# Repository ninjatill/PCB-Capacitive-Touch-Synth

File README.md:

# PCB-Capacitive-Touch-Synth
A Raspberry Pi-based synthesizer with capacitive touch keys directly on a PCB.

## Licensing

### Hardware
All files in `/hardware` are licensed under:

CC BY-NC-SA 4.0

### Firmware
All files in `/firmware` are licensed under:

GPLv3

## Concept
The PCB-Capacitive-Touch-Synth started as a sub-component of a larger science fair project. For my daughter's next science fair project (5th grade), she chose to create Plasma Speakers as we saw on the Franzoli Electronics YouTube page. The plasma speakers are flyback transformers that create a high-voltage arc (which ionizes the air into plasma). The frequeny of the arc creates audio tones. On Franzoli's demonstration videos, he plays MIDI-style music with each speaker acting as a left or right channel/voice. That is the concept we want to re-create.

If we re-create the plasma speakers, then how do we make then into an interactive display for the fair? Well, what if we had 2 midi-controller keyboards hooked up to a host PC. The host PC would do the heavy lifting of audio generation and output to the plasma speakers. Each keyboard would play its notes through either the left or right channel respectively. That's the main idea: 2 keyboards, a host PC, and plasma speakers.

To source the midi keyboards, you could go to Amazon and pick up a 30$-70$ keyboard (higher-end small midi keyboards can run upwards of 200-500$). But, commercial MIDI controllers usually do not output sound directly, it requires a host PC; so its usefullness outside the fair display is limited. The size and scale of the keyboards should be small (to match the entire setup which is portable and compact for a 36"-48" display.) The speakers on Franzoli's demos are very industrial/scientific looking. I thought commercial keyboards would look out of place or be too expensive. So I had a concept of creating keyboards printed on PCBs using capacitive touch buttons. The keyboards would be build to our specific needs and we can build in many features because of the DIY nature.

I decided the best course of action was to have my daughter re-create Fanzoli's Easy-Flyback circuits. It will teach her basic electrical components, schematic creation and PCB layout and fabrication. I think that's a wealth of knowledge for a 10 year old (maybe 11 by the time this comes to fruition). I will handle creating the PCB Capacitive Touch Synthesizer. It is a large complex project and is difficult for my own skill set.

## Documentation

- [Design Notes](docs/design-notes.md)

## Concept to Schematic
As an electrical engineer, I have created PCBs for simple devices. A capacitive touch synthesizer is the largest project/PCB I will have created. So, to jumpstart the project, I consulted my new "friend", ChatGPT. ChatGPT was able to answer questions and make recommendations faster than I could search DigiKey/Mouser, review datasheets, and find the right combination of ICs. But to be clear, I was driving the design. I wanted specific features and ChatGPT helped me realize those features faster than I could alone.

I started with the following design critera
- The front of the keyboard should be as flat as possible both for aestectic and functional reasons.
  - Aesthetically, I don't want a lot of clutter on the front of the board.
  - Functionally, Children will be interacting with this. I don't want exposed chip leads or solder pads. I also don't want through hole components sticking up with sharp edges. If kids can touch it, they will.
- The keyboard should be as small as possible but still allowing for decent usability (key widths wide enough for easy touch, etc.)
  
From the design criteria, we landed with some of the following choices:
- We will use capacitive touch sensors for the piano keys. Capacitive touch reduces mechanical parts that need fabricated (via 3D printing). It's more touch-friendly than many momentary push buttons.
- We will keep all IC's on the back of the board. Only LEDs and a volume knob will protrude from the front.
- We will use only surface mount components (to eliminate protrusions through the board and maintain the flat asthetic.)
- We will 3D print a back cover that serves 2 purposes: 
  - It will cover the back circuitry to prevent tampering.
  - It will raise the PCB off the display surface by a comfortable distance (and tilt it forward a few degrees) to increase usability.

## Basic Functionality
- The synthesizer will funtion in two main modes: standalone and MIDI.
  - In standalone mode, the keyboard will generate its own sounds via speaker or headphones.
  - In MIDI mode, the keyboard will send MIDI commands to a host PC (this is the intended mode for the science fair.

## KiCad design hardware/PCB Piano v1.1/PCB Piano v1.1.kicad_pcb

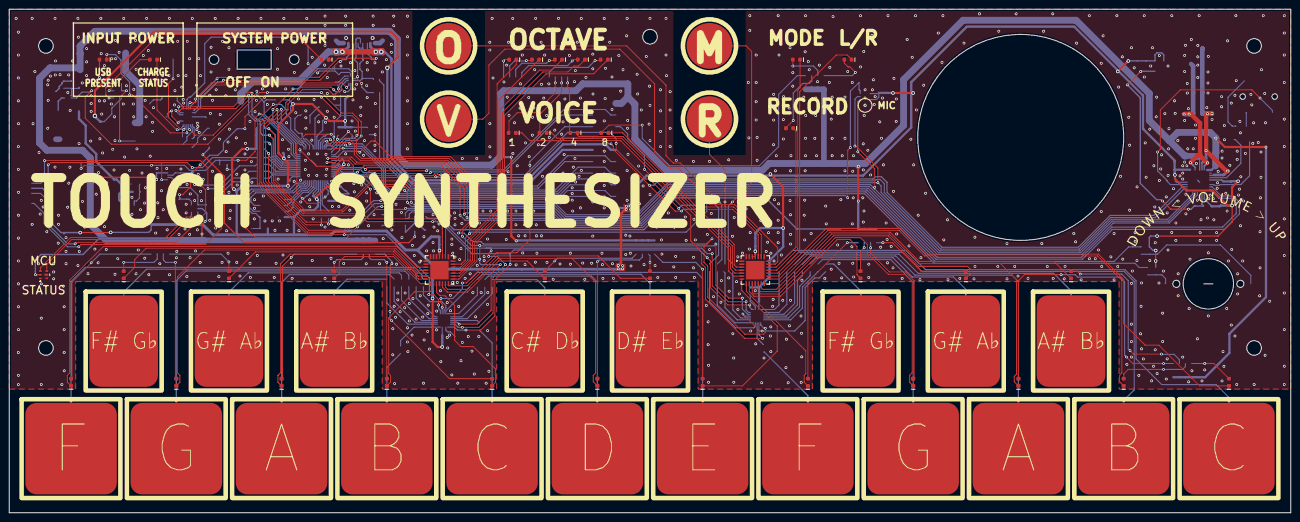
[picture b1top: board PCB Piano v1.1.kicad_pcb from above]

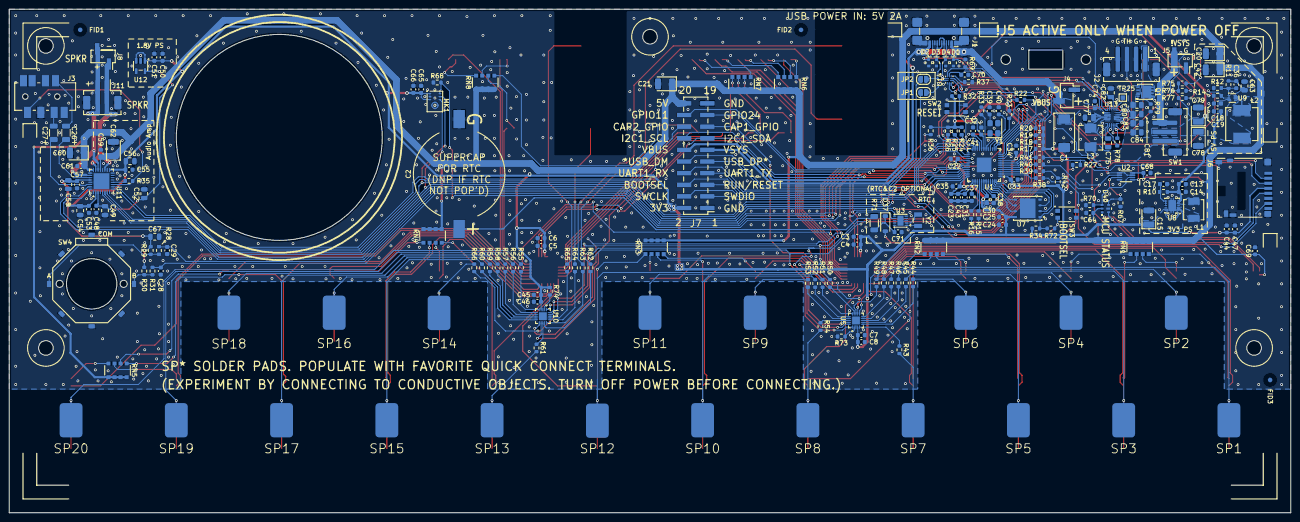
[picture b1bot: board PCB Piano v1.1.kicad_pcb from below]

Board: 2 copper layers, 280.0 x 110.0 mm, 284 parts (216 on the bottom side), 222 nets.

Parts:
C1: 47uF; CP_EIA-7343-43_Kemet-X
C2: 1F; SuperCap_HType_FoldedOutLegs
C3, C6, C8, C13, C18, C23, C24, C31, C37, C44, C45, C50, C66, C74: 1uF; C_0603_1608Metric
C4, C5, C7, C14, C17, C19, C22, C25, C28, C29, C30, C32, C33, C34, C35, C38, C41, C43, C46, C47, C48, C51, C53, C55, C57, C59, C61, C64, C65, C68, C69, C70, C71: .1uF; C_0603_1608Metric
C15, C20, C21, C42, C60, C62, C78, C79: 47uF; CP_EIA-3528-15_AVX-H
C26, C27: 100uF; C_1206_3216Metric
C36: 220pF; C_0603_1608Metric
C39, C40: 27pF; C_0603_1608Metric
C49, C52, C54, C56, C58, C63, C67, C77, C80, C81, C82, C83, C84: 10uF; C_0805_2012Metric
C75: 22nF; C_0805_2012Metric
D1, D2, D3, D4: ESD321; D_SOD-523
D5, D6, D7, D8, D9, D10, D11, D12, D13, D14, D15, D16, D17, D18, D19, D20, D21, D22, D23, D24, D25, D26, D27, D28, D29, D30, D31, D32, D33, D34, D35, D36, D43, D44, D45: 3.3fV 180mcd; LED_0603_1608Metric
D37: Schottky; D_SOD-123
D40, D41: Dotstar LED; APA102-2020
FID1, FID2, FID3: Fiducial; Fiducial_1mm_Mask3mm
H1, H2, H3, H4, H5: MountingHole; MountingHole_3.2mm_M3
J1: USB4110-GF-A; USB_C_Receptacle_GCT_USB4110
J2: JST PH 4-PIN; JST_PH_B4B-PH-SM4-TB_1x04-1MP_P2.00mm_Vertical
J3: 3.5mm TRRS; AudioJack_TRS_Switch_TR1R2S_SJ3-35024K-SMT-TR
J4, J5, J8: PinHeader 1x02 SMT; PinHeader_1x02_P2.54mm_Vertical_SMD_Pin1Right
J6: micro SD Card Slot; microSD_HC_Hirose_DM3D-SF
J7: PinHeader 2x10 SMT Odd_Even; PinHeader_2x10_P2.54mm_Vertical_SMD
J11: JST-PH 2-PIN SMT; JST_PH_B2B-PH-SM4-TB_1x02-1MP_P2.00mm_Vertical
JP1, JP2: SolderJumper_2_Open; SolderJumper-2_P1.3mm_Open_RoundedPad1.0x1.5mm
L1: 2.2uH; L_Bourns_SRP4020T_4.06x4.45x2.0mm
L2: 2.2uH; L_Pulse_BMRB00060630_7.3x6.6mm
L3: 1uH; L_Sumida_0530CDMCCDS-1R0MC_5.4x5.2mm
MK1: MEMS I2S Microphone; InvenSense_ICS-43432-7_4x3mm
Q1: P-Ch Power MOSFET; PPAK_3x3
R10: 100; R_0603_1608Metric
R11: 732k; R_0603_1608Metric
R12, R14, R25, R26, R27, R36, R37, R67, R69, R70, R73, R74, R79: 100k; R_0603_1608Metric
R15, R16, R38, R39, R40, R41: 27; R_0603_1608Metric
R17, R18, R19, R20: 4.7k; R_0603_1608Metric
R22, R23, R24, R28, R29, R30, R31, R32, R34, R42, R43, R44, R45, R46, R47, R48, R49, R50, R51, R52, R53, R54, R55, R56, R57, R58, R59, R60, R61, R62, R63, R64, R65, R66, R68, R78: 10k; R_0603_1608Metric
R33, R72: 1k; R_0603_1608Metric
R35: 2.2k; R_0603_1608Metric
R71: 150; R_1206_3216Metric
R75, R76, R77: 1.5k; R_0603_1608Metric
RN1, RN2, RN3, RN4, RN5, RN6, RN7, RN8: 180 Ohm; R_Array_Convex_4x1206
SP1, SP2, SP3, SP4, SP5, SP6, SP7, SP8, SP9, SP10, SP11, SP12, SP13, SP14, SP15, SP16, SP17, SP18, SP19, SP20: Pad_Solder_SMT_5x7mm
SW1: JST-PH 1x03 SMT; JST_PH_B3B-PH-SM4-TB_1x03-1MP_P2.00mm_Vertical
SW2, SW3: Pushbutton MO; SW_SWT0115-020025SSA_REVA
SW4: MER1045-24; Switch_RotaryEncoder_MER1045-24
SWCUT1: MFS 126 D; Switch_Slide_MFS126E_PanelCutout
TP1, TP3, TP5, TP7, TP8, TP10, TP12, TP13, TP15, TP17, TP19, TP20: Touchpad_WhiteKey
TP2, TP4, TP6, TP9, TP11, TP14, TP16, TP18: Touchpad_BlackKey
TP21, TP22, TP23, TP24: Touchpad_Circle_10mm
TP25: TestPoint_Square; TestPoint_Pad_1.0x1.0mm
U1: RP2040; QFN-56-1EP_7x7mm_P0.4mm_EP3.2x3.2mm
U2: Dual Line Buffer; VSSOP-8_2.3x2mm_P0.5mm
U3: RTC; DFN-10-1EP_2.6x2.6mm_P0.5mm_EP1.3x2.2mm
U4, U6: LED Controller; NXP_HVQFN-28_6mmx6mmx0.85mm
U5, U10: Touch Controller; VQFN-20-1EP_3x3mm_P0.4mm_EP1.7x1.7mm
U7: 128MBit; WSON-8-1EP_6x5mm_P1.27mm_EP3.4x4.3mm
U8: 3.3V; Texas_DRC0010J
U9: 5V; SOT-563
U11: Audio DAC Class-D I2S/I2C; Texas_RHB0032E_VQFN-32-1EP_5x5mm_P0.5mm_EP3.45x3.45mm
U12: 1.8V; SOT-23-5
U13: USB C Sink Ctrl/Batt Chgr; QFN-22_2.5x3.2mm_P0.4mm
U14: 1:2 USB MUX; TQFN-10_ZL_1.6x1.3mm_P0.4mm
Y1: 12MHz; Crystal_SMD_Abracon_ABM8G-4Pin_3.2x2.5mm
Y2: 32.768kHz; Crystal_Kyocera_DT32_3.2x1.5mm

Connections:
+1V1: C37.1, C38.1, C41.1, U1.23 (DVDD), U1.45 (VREG_VOUT), U1.50 (DVDD)
+1V8: C48.1, C49.1, C52.1, U11.3 (DVDD), U12.5 (OUT)
+3.3V: C3.1, C4.1, C5.1, C6.1, C7.1, C8.1, C15.1, C22.1, C23.1, C24.1, C25.1, C30.1, C31.1, C32.1, C33.1, C34.1, C35.1, C43.1, C44.1, C45.1, C46.1, C47.1, C50.1, C51.1, C53.1, C54.1, C55.1, C56.1, C57.1, C58.1, C65.1, C66.1, C67.1, J6.4 (VDD), J7.2, MK1.1 (LR), MK1.3 (VDD), R17.1, R18.1, R19.1, R20.1, R22.1, R23.1, R24.1, R25.1, R26.1, R27.1, R29.2, R30.2, R32.1, R34.1, R36.1, R42.1, R74.1, U1.1 (IOVDD), U1.10 (IOVDD), U1.22 (IOVDD), U1.33 (IOVDD), U1.42 (IOVDD), U1.43 (ADC_AVDD), U1.44 (VREG_VIN), U1.48 (USB_VDD), U1.49 (IOVDD), U4.25 (VDD), U5.4 (VDD), U6.25 (VDD), U6.26 (A0), U7.8 (VCC), U8.1 (VOUT), U8.10 (FB), U10.4 (VDD), U11.2 (IOVDD), U11.17 (AVDD), U11.28 (HPVDD), U12.1 (IN), U12.3 (EN)
+5V: C20.1, C21.1, C36.1, C42.1, C59.1, C60.1, C61.1, C62.1, C63.1, C64.1, C68.1, C69.1, D40.2 (VDD), D41.2 (VDD), J7.20, R11.1, RN1.5 (R4.2), RN1.6 (R3.2), RN1.7 (R2.2), RN1.8 (R1.2), RN2.5 (R4.2), RN2.6 (R3.2), RN2.7 (R2.2), RN2.8 (R1.2), RN3.5 (R4.2), RN3.6 (R3.2), RN3.7 (R2.2), RN3.8 (R1.2), RN4.5 (R4.2), RN4.6 (R3.2), RN4.7 (R2.2), RN4.8 (R1.2), RN5.5 (R4.2), RN5.6 (R3.2), RN5.7 (R2.2), RN5.8 (R1.2), RN6.5 (R4.2), RN6.6 (R3.2), RN6.7 (R2.2), RN6.8 (R1.2), RN7.5 (R4.2), RN7.6 (R3.2), RN7.7 (R2.2), RN7.8 (R1.2), RN8.5 (R4.2), RN8.6 (R3.2), RN8.7 (R2.2), RN8.8 (R1.2), U2.8 (VCC), U9.6 (VOUT), U11.21 (SPKVDD), U11.24 (SPKVDD)
/LED/I2C1_SCL: J7.14, R20.2, U1.9 (GPIO7), U3.7 (SCL), U4.23 (SCL), U6.23 (SCL), U11.10 (SCL), U13.16 (SCL)
/LED/I2C1_SDA: J7.13, R19.2, U1.8 (GPIO6), U3.6 (SDA), U4.24 (SDA), U6.24 (SDA), U11.9 (SDA), U13.15 (SDA)
/LED/LED_100: D5.1 (K), U4.3 (LED0)
/LED/LED_101: D6.1 (K), U4.4 (LED1)
/LED/LED_102: D7.1 (K), U4.5 (LED2)
/LED/LED_103: D8.1 (K), U4.6 (LED3)
/LED/LED_104: D9.1 (K), U4.7 (LED4)
/LED/LED_105: D10.1 (K), U4.8 (LED5)
/LED/LED_106: D11.1 (K), U4.9 (LED6)
/LED/LED_107: D12.1 (K), U4.10 (LED7)
/LED/LED_108: D13.1 (K), U4.12 (LED8)
/LED/LED_109: D14.1 (K), U4.13 (LED9)
/LED/LED_110: D15.1 (K), U4.14 (LED10)
/LED/LED_111: D29.1 (K), U4.15 (LED11)
/LED/LED_112: D28.1 (K), U4.16 (LED12)
/LED/LED_113: D27.1 (K), U4.17 (LED13)
/LED/LED_114: D26.1 (K), U4.18 (LED14)
/LED/LED_115: D25.1 (K), U4.19 (LED15)
/LED/LED_200: D30.1 (K), U6.3 (LED0)
/LED/LED_201: D31.1 (K), U6.4 (LED1)
/LED/LED_202: D32.1 (K), U6.5 (LED2)
/LED/LED_203: D33.1 (K), U6.6 (LED3)
/LED/LED_204: D16.1 (K), U6.7 (LED4)
/LED/LED_205: D17.1 (K), U6.8 (LED5)
/LED/LED_206: D18.1 (K), U6.9 (LED6)
/LED/LED_207: D19.1 (K), U6.10 (LED7)
/LED/LED_208: D20.1 (K), U6.12 (LED8)
/LED/LED_209: D21.1 (K), U6.13 (LED9)
/LED/LED_210: D22.1 (K), U6.14 (LED10)
/LED/LED_211: D23.1 (K), U6.15 (LED11)
/LED/LED_212: D24.1 (K), U6.16 (LED12)
/LED/LED_213: D36.1 (K), U6.17 (LED13)
/LED/LED_214: D35.1 (K), U6.18 (LED14)
/LED/LED_215: D34.1 (K), U6.19 (LED15)
/LED/LED_~EN: R36.2, U1.31 (GPIO20), U4.20 (~OE), U6.20 (~OE)
/MCU/5V_EN: R14.2, U1.30 (GPIO19), U9.2 (EN)
/MCU/AMP_INT: U1.41 (GPIO29/ADC3), U11.32 (GPIO1)
/MCU/AMP_~RST: U1.37 (GPIO25), U11.31 (~RESET)
/MCU/BOOTSEL: J7.6, R72.2, SW3.3
/MCU/CAP1_~INT: R23.2, U1.18 (GPIO15), U5.11 (*INT)
/MCU/CAP2_~INT: R24.2, U1.27 (GPIO16), U10.11 (*INT)
/MCU/CAPx_~RST: R25.2, U1.28 (GPIO17), U5.19 (*RESET), U10.19 (*RESET)
/MCU/CHG_~INT: R22.2, U1.12 (GPIO9), U13.8 (~INT)
/MCU/DS_~EN: R26.2, U1.29 (GPIO18), U2.1, U2.7
/MCU/ENC_A: C29.1, R28.2, U1.32 (GPIO21)
/MCU/ENC_B: C28.1, R31.1, U1.34 (GPIO22)
/MCU/GPIO11: J7.18, U1.14 (GPIO11)
/MCU/GPIO24: J7.17, U1.36 (GPIO24)
/MCU/I2C0_SCL: R18.2, U1.7 (GPIO5), U5.1 (SCL), U10.1 (SCL)
/MCU/I2C0_SDA: R17.2, U1.6 (GPIO4), U5.20 (SDA), U10.20 (SDA)
/MCU/I2S_BCLK: MK1.6 (SCK), U1.38 (GPIO26/ADC0), U11.7 (BCLK)
/MCU/I2S_LRCLK: MK1.5 (WS), U1.39 (GPIO27/ADC1), U11.6 (WCLK)
/MCU/I2S_SDATA: U1.40 (GPIO28/ADC2), U11.5 (DIN)
/MCU/I2S_SDATA_MIC: MK1.7 (SD), R68.2, U1.35 (GPIO23)
/MCU/MCU_DM: R15.2, U14.6 (D-)
/MCU/MCU_DP: R16.2, U14.7 (D+)
/MCU/RTC_BATT: C2.1, R71.1
/MCU/RTC_VDD: C71.1, D37.1 (K), R71.2, U3.10 (VDD)
/MCU/RUN: J7.5, R32.2, SW2.3, U1.26 (RUN)
/MCU/SD_DET: J6.10 (DET_A), R27.2, U1.11 (GPIO8)
/MCU/SPI0_MISO: J6.7 (DAT0), R38.1
/MCU/SPI0_MOSI: J6.3 (CMD), R41.1, U2.5
/MCU/SPI0_SCK: J6.5 (CLK), R40.1, U2.2
/MCU/SPI0_~CS: J6.2 (DAT3/CD), R39.1, R42.2
/MCU/SWCLK: J7.4, U1.24 (SWCLK)
/MCU/SWDIO: J7.3, U1.25 (SWDIO)
/MCU/UART1_RX: J7.8, U1.16 (GPIO13)
/MCU/UART1_TX: J7.7, U1.15 (GPIO12)
/MCU/USB_SEL: R69.1, U1.13 (GPIO10), U14.10 (SEL)
/audio/HP_L: C26.1, U11.27 (HPL)
/audio/HP_R: C27.1, U11.30 (HPR)
/audio/SPKM: J8.1, J11.1, U11.19 (SPKM), U11.23 (SPKM)
/audio/SPKP: J8.2, J11.2, U11.22 (SPKP), U11.26 (SPKP)
/debug/CAP1_GPIO: J7.15, U5.12 (GPIO12)
/debug/CAP2_GPIO: J7.16, U10.12 (GPIO12)
/debug/DEBUG_DM: J7.10, JP2.1 (A)
/debug/DEBUG_DP: J7.9, JP1.1 (A)
/power/USB_CC1: D1.1 (K), J1.A5 (CC1), U13.1 (CC1)
/power/USB_CC2: D2.1 (K), J1.B5 (CC2), U13.22 (CC2)
/power/USB_DM: D3.1 (K), J1.A6 (D+), J1.B6 (D+), JP2.2 (B), U14.2 (Y-)
/power/USB_DP: D4.1 (K), J1.A7 (D-), J1.B7 (D-), JP1.2 (B), U14.1 (Y+)
/power/battery charger 2/BATT_POS: J2.1, Q1.D
/power/battery charger 2/CHG_BATT: C80.1, C81.1, Q1.S, U13.12 (BATTSNS), U13.14 (BATT)
/power/battery charger 2/CHG_DM: U13.20 (D-), U14.4 (M-)
/power/battery charger 2/CHG_DP: U13.21 (D+), U14.5 (M+)
/power/battery charger 2/CHG_OUT: C83.1, C84.1, D37.2 (A), L3.1, R75.1, R76.1, SW1.3 (C), U13.13 (SYS)
/power/battery charger 2/CHG_VCC: C70.1, C82.1, U13.19 (VCC), U14.9 (VDD)
/power/battery charger 2/TH1_POS: J2.3, R78.2, U13.10 (NTC1)
/touch/TOUCH_100: R43.2, SP7.1 (1_1), TP7.1
/touch/TOUCH_101: R44.2, SP6.1 (1_1), TP6.1
/touch/TOUCH_102: R45.2, SP5.1 (1_1), TP5.1
/touch/TOUCH_103: R46.2, SP4.1 (1_1), TP4.1
/touch/TOUCH_104: R47.2, SP3.1 (1_1), TP3.1
/touch/TOUCH_105: R48.2, SP2.1 (1_1), TP2.1
/touch/TOUCH_106: R49.2, SP1.1 (1_1), TP1.1
/touch/TOUCH_107: R50.2, SP12.1 (1_1), TP12.1
/touch/TOUCH_108: R51.2, SP11.1 (1_1), TP11.1
/touch/TOUCH_109: R52.2, SP10.1 (1_1), TP10.1
/touch/TOUCH_110: R53.2, SP9.1 (1_1), TP9.1
/touch/TOUCH_111: R54.2, SP8.1 (1_1), TP8.1
/touch/TOUCH_200: R55.2, SP20.1 (1_1), TP20.1
/touch/TOUCH_201: R56.2, SP19.1 (1_1), TP19.1
/touch/TOUCH_202: R57.2, SP18.1 (1_1), TP18.1
/touch/TOUCH_203: R58.2, SP17.1 (1_1), TP17.1
/touch/TOUCH_204: R59.2, SP16.1 (1_1), TP16.1
/touch/TOUCH_205: R60.2, SP15.1 (1_1), TP15.1
/touch/TOUCH_206: R61.2, SP13.1 (1_1), TP13.1
/touch/TOUCH_207: R62.2, TP22.1
/touch/TOUCH_208: R63.2, TP21.1
/touch/TOUCH_209: R64.2, TP24.1
/touch/TOUCH_210: R65.2, TP23.1
/touch/TOUCH_211: R66.2, SP14.1 (1_1), TP14.1
GND: C1.2, C2.2, C3.2, C4.2, C5.2, C6.2, C7.2, C8.2, C13.2, C14.2, C15.2, C17.2, C18.2, C19.2, C20.2, C21.2, C22.2, C23.2, C24.2, C25.2, C28.2, C29.2, C30.2, C31.2, C32.2, C33.2, C34.2, C35.2, C37.2, C38.2, C39.2, C40.2, C41.2, C42.2, C43.2, C44.2, C45.2, C46.2, C47.2, C48.2, C49.2, C50.2, C51.2, C52.2, C53.2, C54.2, C55.2, C56.2, C57.2, C58.2, C59.2, C60.2, C61.2, C62.2, C63.2, C64.2, C65.2, C66.2, C67.2, C68.2, C69.2, C70.2, C71.2, C74.2, C77.2, C78.2, C79.2, C80.2, C81.2, C82.2, C83.2, C84.2, D1.2 (A), D2.2 (A), D3.2 (A), D4.2 (A), D40.5 (GND), D41.5 (GND), D45.1 (K), J1.A1 (GND), J1.A12 (GND), J1.B1 (GND), J1.B12 (GND), J1.SH (SHIELD), J2.2, J2.4, J2.MP (MountPin), J3.2 (R2), J4.1, J5.1, J6.6 (VSS), J6.9 (DET_B), J6.SH (SHIELD), J7.1, J7.19, J11.MP (MountPin), MK1.2 (CONFIG), MK1.4 (GND), R12.1, R14.1, R37.1, R67.2, R68.1, R69.2, R70.2, R73.2, R79.2, SW1.MP, SW2.1, SW2.2, SW3.1, SW3.2, SW4.C, SW4.GND (MountPoints), U1.19 (TESTEN), U1.57 (GND), U2.4 (GND), U3.3 (CLKOE), U3.5 (VSS), U3.11 (EP), U4.1 (A3), U4.2 (A4), U4.11 (VSS), U4.21 (A5), U4.22 (EXTCLK), U4.26 (A0), U4.27 (A1), U4.28 (A2), U4.29 (VSS), U5.3 (GND), U5.21 (EP), U6.1 (A3), U6.2 (A4), U6.11 (VSS), U6.21 (A5), U6.22 (EXTCLK), U6.27 (A1), U6.28 (A2), U6.29 (VSS), U7.4 (GND), U7.9 (EP), U8.3 (PGND), U8.9 (GND), U8.11 (PGND), U9.4 (GND), U10.3 (GND), U10.21 (EP), U11.1 (IOVSS), U11.16 (AVSS), U11.18 (DVSS), U11.20 (SPKVSS), U11.25 (SPKVSS), U11.29 (HPVSS), U11.33 (EP), U12.2 (GND), U13.5 (PGND), U13.18 (AGND), U14.3 (GND), Y1.2 (G), Y1.4 (G)
unnamed: C39.1, R33.1, Y1.3
unnamed: D5.2 (A), RN1.4 (R4.1)
unnamed: D6.2 (A), RN1.3 (R3.1)
unnamed: D7.2 (A), RN1.2 (R2.1)
unnamed: D8.2 (A), RN1.1 (R1.1)
unnamed: D9.2 (A), RN2.4 (R4.1)
unnamed: D10.2 (A), RN2.3 (R3.1)
unnamed: D11.2 (A), RN2.2 (R2.1)
unnamed: D12.2 (A), RN2.1 (R1.1)
unnamed: D13.2 (A), RN3.4 (R4.1)
unnamed: D14.2 (A), RN3.3 (R3.1)
unnamed: D15.2 (A), RN3.2 (R2.1)
unnamed: D16.2 (A), RN3.1 (R1.1)
unnamed: D17.2 (A), RN4.4 (R4.1)
unnamed: D18.2 (A), RN4.3 (R3.1)
unnamed: D19.2 (A), RN4.2 (R2.1)
unnamed: D20.2 (A), RN4.1 (R1.1)
unnamed: D21.2 (A), RN5.1 (R1.1)
unnamed: D22.2 (A), RN5.2 (R2.1)
unnamed: D23.2 (A), RN5.3 (R3.1)
unnamed: D24.2 (A), RN5.4 (R4.1)
unnamed: D25.2 (A), RN6.1 (R1.1)
unnamed: D26.2 (A), RN6.2 (R2.1)
unnamed: D27.2 (A), RN6.3 (R3.1)
unnamed: D28.2 (A), RN6.4 (R4.1)
unnamed: D29.2 (A), RN7.1 (R1.1)
unnamed: D30.2 (A), RN8.1 (R1.1)
unnamed: D31.2 (A), RN7.4 (R4.1)
unnamed: D32.2 (A), RN7.3 (R3.1)
unnamed: D33.2 (A), RN7.2 (R2.1)
unnamed: D34.2 (A), RN8.2 (R2.1)
unnamed: D35.2 (A), RN8.3 (R3.1)
unnamed: D36.2 (A), RN8.4 (R4.1)
unnamed: D40.3 (CKI), R70.1, U2.6
unnamed: D40.1 (CKO), D41.3 (CKI)
unnamed: D40.6 (SDI), R67.1, U2.3
unnamed: D40.4 (SDO), D41.6 (SDI)
unnamed: D43.2 (A), R75.2
unnamed: D43.1 (K), U13.9 (PG/NTC2)
unnamed: D44.2 (A), R76.2
unnamed: D44.1 (K), U13.11 (STAT/IB)
unnamed: D45.2 (A), R77.2
unnamed: C27.2, J3.3 (R1)
unnamed: J3.1 (S), R35.2, U11.11 (VOL/MICDET)
unnamed: C26.2, J3.8 (T)
unnamed: J5.2, SW1.1 (A)
unnamed: Q1.G, R79.1
unnamed: R28.1, R29.1, SW4.A
unnamed: R30.1, R31.2, SW4.B
unnamed: R38.2, U1.2 (GPIO0)
unnamed: R39.2, U1.3 (GPIO1)
unnamed: R40.2, U1.4 (GPIO2)
unnamed: R41.2, U1.5 (GPIO3)
unnamed: U1.52 (QSPI_SCLK), U7.6 (CLK)
unnamed: U1.53 (QSPI_SD0), U7.5 (DI/IO_{0})
unnamed: U1.55 (QSPI_SD1), U7.2 (DO/IO_{1})
unnamed: U1.54 (QSPI_SD2), U7.3 (~WP/IO_{2})
unnamed: U1.51 (QSPI_SD3), U7.7 (~HOLD/~RESET/IO_{3})
unnamed: R16.1, U1.46 (USB_DM)
unnamed: R15.1, U1.47 (USB_DP)
unnamed: C40.1, U1.20 (XIN), Y1.1
unnamed: R33.2, U1.21 (XOUT)
unnamed: R34.2, R72.1, U1.56 (~QSPI_SS), U7.1 (~CS)
unnamed: U3.1 (OSCI), Y2.2
unnamed: U3.2 (OSCO), Y2.1
unnamed: R73.1, U5.2 (ADD_SEL)
unnamed: R43.1, U5.5 (BUTTON0)
unnamed: R44.1, U5.6 (BUTTON1)
unnamed: R45.1, U5.7 (BUTTON2)
unnamed: R46.1, U5.8 (BUTTON3)
unnamed: R47.1, U5.9 (BUTTON4)
unnamed: R48.1, U5.10 (BUTTON5)
unnamed: R49.1, U5.13 (BUTTON6)
unnamed: R50.1, U5.14 (BUTTON7)
unnamed: R51.1, U5.15 (BUTTON8)
unnamed: R52.1, U5.16 (BUTTON9)
unnamed: R53.1, U5.17 (BUTTON10)
unnamed: R54.1, U5.18 (BUTTON11)
unnamed: C17.1, R10.2, U8.6 (EN), U8.7 (PS/SYNC), U8.8 (VINA)
unnamed: L1.1, U8.4 (L1)
unnamed: L1.2, U8.2 (L2)
unnamed: C36.2, R11.2, R12.2, U9.1 (FB)
unnamed: L2.1, U9.5 (SW)
unnamed: R74.2, U10.2 (ADD_SEL)
unnamed: R55.1, U10.5 (BUTTON0)
unnamed: R56.1, U10.6 (BUTTON1)
unnamed: R57.1, U10.7 (BUTTON2)
unnamed: R58.1, U10.8 (BUTTON3)
unnamed: R59.1, U10.9 (BUTTON4)
unnamed: R60.1, U10.10 (BUTTON5)
unnamed: R61.1, U10.13 (BUTTON6)
unnamed: R62.1, U10.14 (BUTTON7)
unnamed: R63.1, U10.15 (BUTTON8)
unnamed: R64.1, U10.16 (BUTTON9)
unnamed: R65.1, U10.17 (BUTTON10)
unnamed: R66.1, U10.18 (BUTTON11)
unnamed: R35.1, U11.12 (MICBIAS)
unnamed: R78.1, U13.7 (VRNTC)
unnamed: TP25.1 (1_1), U13.17 (~RST)
unnamed: C75.1, U13.6 (BST)
unnamed: C77.1, U13.3 (PMID)
unnamed: C75.2, L3.2, U13.4 (SW)
unnamed: R37.2, U14.8 (~OE)
VBUS: C1.1, C74.1, J1.A4 (VBUS), J1.A9 (VBUS), J1.B4 (VBUS), J1.B9 (VBUS), J4.2, J7.12, U13.2 (IN)
VSYS: C13.1, C14.1, C18.1, C19.1, C78.1, C79.1, J7.11, L2.2, R10.1, R77.1, SW1.2 (B), U8.5 (VIN), U9.3 (VIN)

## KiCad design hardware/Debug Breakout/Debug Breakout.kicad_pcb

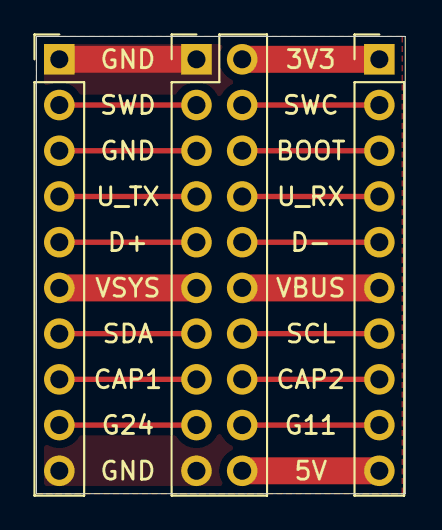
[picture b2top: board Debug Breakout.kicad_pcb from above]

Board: 2 copper layers, 20.5 x 25.4 mm, 3 parts (0 on the bottom side), 19 nets.

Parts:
J1: PinHeader_2x10_P2.54mm_Vertical
J2, J3: Conn_01x10; PinHeader_1x10_P2.54mm_Vertical

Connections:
+3.3V: J1.2, J2.1
+5V: J1.20, J2.10
/BOOTSEL: J1.6, J2.3
/CAP1_GPIO: J1.15, J3.8
/CAP2_GPIO: J1.16, J2.8
/DEBUG_DM: J1.10, J2.5
/DEBUG_DP: J1.9, J3.5
/GPIO11: J1.18, J2.9
/GPIO24: J1.17, J3.9
/I2C1_SCL: J1.14, J2.7
/I2C1_SDA: J1.13, J3.7
/RUN: J1.5, J3.3
/SWCKL: J1.4, J2.2
/SWDIO: J1.3, J3.2
/UART1_RX: J1.8, J2.4
/UART1_TX: J1.7, J3.4
GND: J1.1, J1.19, J3.1, J3.10
VBUS: J1.12, J2.6
VSYS: J1.11, J3.6

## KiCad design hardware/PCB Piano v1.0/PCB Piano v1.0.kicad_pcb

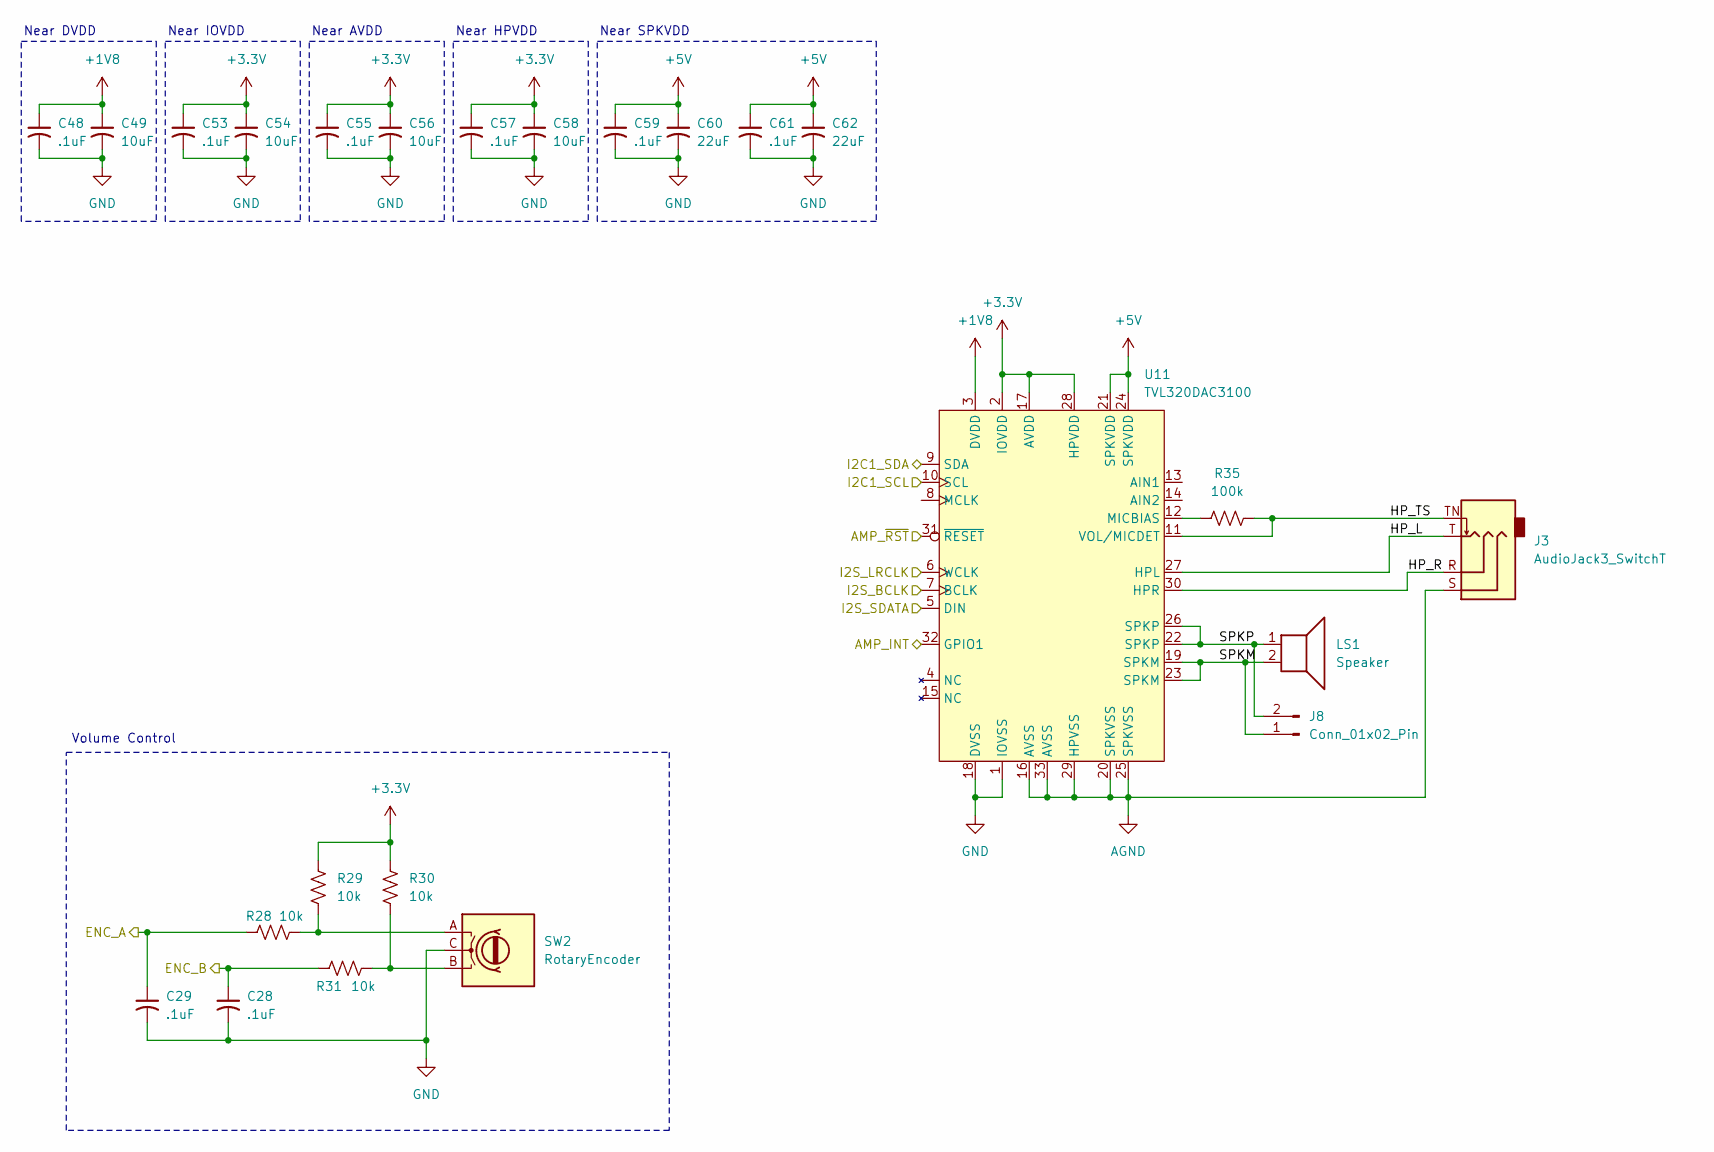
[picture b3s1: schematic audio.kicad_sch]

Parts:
C28, C29, C48, C53, C55, C57, C59, C61: .1uF; C_0603_1608Metric
C49, C54, C56, C58: 10uF; C_0603_1608Metric
C60, C62: 22uF; CP_EIA-6032-20_AVX-F
J3: AudioJack3_SwitchT; Jack_3.5mm_CUI_SJ-3524-SMT_Horizontal
J8: Conn_01x02_Pin; JST_SH_BM03B-SRSS-TB_1x03-1MP_P1.00mm_Vertical
LS1: Speaker; TestPoint_2Pads_2.5mmx2.5mm_5mmSpacing
R28, R29, R30, R31: 10k; R_0603_1608Metric
R35: 100k; R_0603_1608Metric
SW2: RotaryEncoder; Switch_RotaryEncoder_MER1045-24
U11: TVL320DAC3100; Texas_RHB0032E_VQFN-32-1EP_5x5mm_P0.5mm_EP3.45x3.45mm

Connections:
+1V8: C48.1, C49.1, U11.3 (DVDD); also elsewhere on the board
+3.3V: C53.1, C54.1, C55.1, C56.1, C57.1, C58.1, R29.2, R30.2, U11.2 (IOVDD), U11.17 (AVDD), U11.28 (HPVDD); also elsewhere on the board
+5V: C59.1, C60.1, C61.1, C62.1, U11.21 (SPKVDD), U11.24 (SPKVDD); also elsewhere on the board
/LED/I2C1_SCL: U11.10 (SCL); also elsewhere on the board
/LED/I2C1_SDA: U11.9 (SDA); also elsewhere on the board
/MCU/AMP_INT: U11.32 (GPIO1); also elsewhere on the board
/MCU/AMP_~RST: U11.31 (~RESET); also elsewhere on the board
/MCU/ENC_A: C29.1, R28.2; also elsewhere on the board
/MCU/ENC_B: C28.1, R31.1; also elsewhere on the board
/MCU/I2S_BCLK: U11.7 (BCLK); also elsewhere on the board
/MCU/I2S_LRCLK: U11.6 (WCLK); also elsewhere on the board
/MCU/I2S_SDATA: U11.5 (DIN); also elsewhere on the board
/audio/HP_L: J3.T, U11.27 (HPL)
/audio/HP_R: J3.R, U11.30 (HPR)
/audio/HP_TS: J3.TN, R35.2, U11.11 (VOL/MICDET)
/audio/SPKM: J8.1, LS1.2, U11.19 (SPKM), U11.23 (SPKM)
/audio/SPKP: J8.2, LS1.1, U11.22 (SPKP), U11.26 (SPKP)
AGND: J3.S, U11.16 (AVSS), U11.20 (SPKVSS), U11.25 (SPKVSS), U11.29 (HPVSS), U11.33 (AVSS)
GND: C28.2, C29.2, C48.2, C49.2, C53.2, C54.2, C55.2, C56.2, C57.2, C58.2, C59.2, C60.2, C61.2, C62.2, SW2.C, U11.1 (IOVSS), U11.18 (DVSS); also elsewhere on the board
unnamed: R28.1, R29.1, SW2.A
unnamed: R30.1, R31.2, SW2.B
unnamed: R35.1, U11.12 (MICBIAS)

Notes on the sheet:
Near SPKVDD
Near AVDD
Near IOVDD
Volume Control
Near DVDD
Near HPVDD

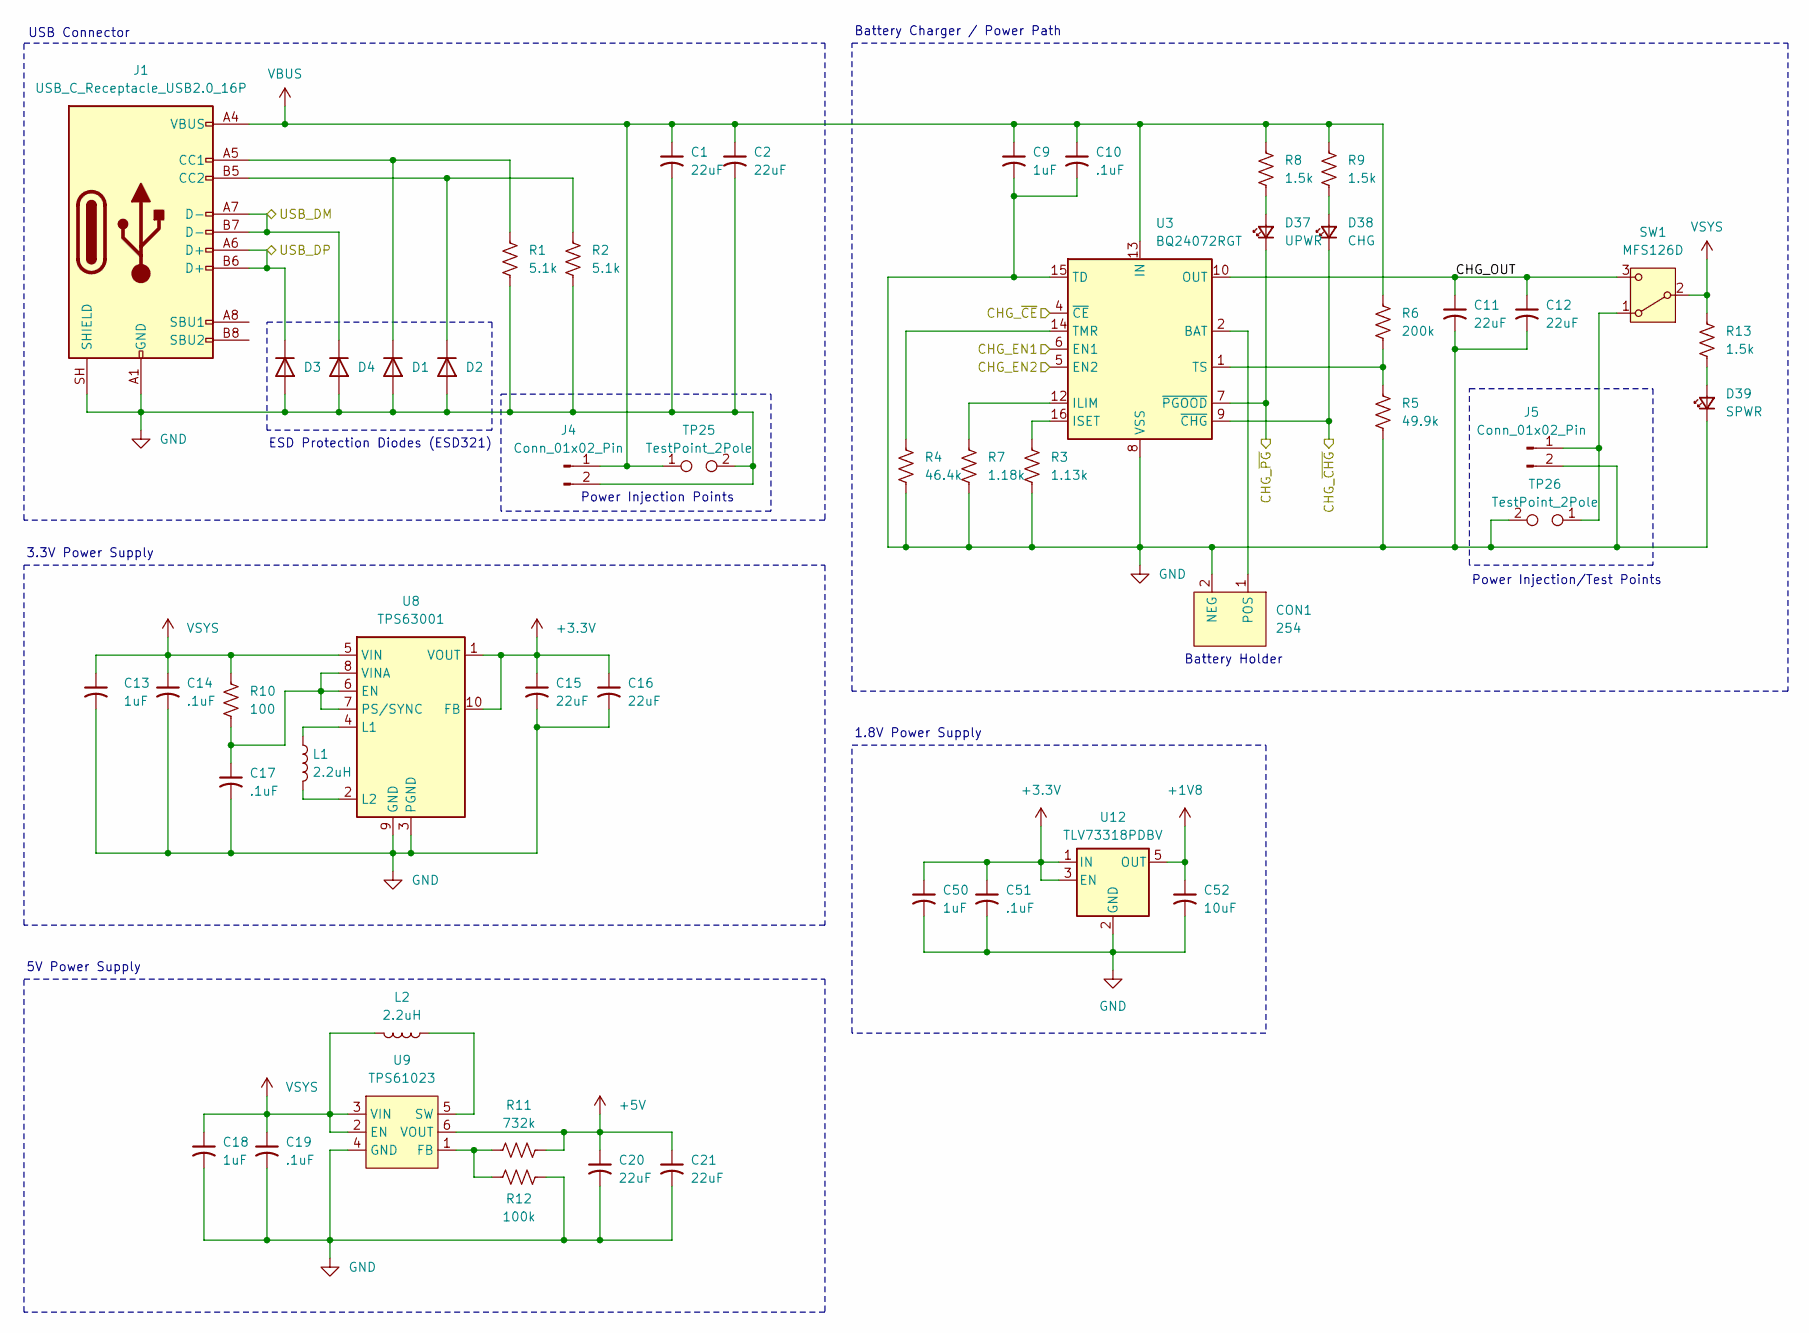
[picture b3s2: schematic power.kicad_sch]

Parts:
C1, C2, C11, C12, C15, C16, C20, C21: 22uF; CP_EIA-6032-20_AVX-F
C9, C13, C18, C50: 1uF; C_0603_1608Metric
C10, C14, C17, C19, C51: .1uF; C_0603_1608Metric
C52: 10uF; C_0603_1608Metric
CON1: 254; BatteryHolder_254Clips_18650Battery
D1, D2, D3, D4: D_SOD-523
D37: UPWR; LED_0603_1608Metric
D38: CHG; LED_0603_1608Metric
D39: SPWR; LED_0603_1608Metric
J1: USB_C_Receptacle_USB2.0_16P; USB_C_Receptacle_GCT_USB4110
J4, J5: Conn_01x02_Pin; PinHeader_1x02_P2.54mm_Vertical_SMD_Pin1Left
L1, L2: 2.2uH; L_1008_2520Metric
R1, R2: 5.1k; R_0603_1608Metric
R3: 1.13k; R_0603_1608Metric
R4: 46.4k; R_0603_1608Metric
R5: 49.9k; R_0603_1608Metric
R6: 200k; R_0603_1608Metric
R7: 1.18k; R_0603_1608Metric
R8, R9, R13: 1.5k; R_0603_1608Metric
R10: 100; R_0603_1608Metric
R11: 732k; R_0603_1608Metric
R12: 100k; R_0603_1608Metric
SW1: MFS126D; SolderPoint_3Pads_2.54x2.54_5.08Spacing
TP25, TP26: TestPoint_2Pole; TestPoint_2Pads_2.5mmx2.5mm_5mmSpacing
U3: BQ24072RGT; VQFN-16-1EP_3x3mm_P0.5mm_EP1.6x1.6mm
U8: TPS63001; Texas_DRC0010J_ThermalVias
U9: TPS61023; SOT-563
U12: TLV73318PDBV; SOT-23-5

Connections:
+1V8: C52.1, U12.5 (OUT); also elsewhere on the board
+3.3V: C15.1, C16.1, C50.1, C51.1, U8.1 (VOUT), U8.10 (FB), U12.1 (IN), U12.3 (EN); also elsewhere on the board
+5V: C20.1, C21.1, R11.1, U9.6 (VOUT); also elsewhere on the board
/MCU/CHG_EN1: U3.6 (EN1); also elsewhere on the board
/MCU/CHG_EN2: U3.5 (EN2); also elsewhere on the board
/MCU/CHG_~CE: U3.4 (~CE); also elsewhere on the board
/MCU/CHG_~CHG: D38.1 (K), U3.9 (~CHG); also elsewhere on the board
/MCU/CHG_~PG: D37.1 (K), U3.7 (~PGOOD); also elsewhere on the board
/MCU/USB_DM: D4.1 (K), J1.A7 (D-), J1.B7 (D-); also elsewhere on the board
/MCU/USB_DP: D3.1 (K), J1.A6 (D+), J1.B6 (D+); also elsewhere on the board
/power/CHG_OUT: C11.1, C12.1, SW1.3 (C), U3.10 (OUT), U3.11 (OUT)
GND: C1.2, C2.2, C9.2, C10.2, C11.2, C12.2, C13.2, C14.2, C15.2, C16.2, C17.2, C18.2, C19.2, C20.2, C21.2, C50.2, C51.2, C52.2, CON1.2 (NEG), D1.2 (A), D2.2 (A), D3.2 (A), D4.2 (A), D39.1 (K), J1.A1 (GND), J1.A12 (GND), J1.B1 (GND), J1.B12 (GND), J1.SH (SHIELD), J4.2, J5.2, R1.2, R2.2, R3.2, R4.2, R5.2, R7.2, R12.1, TP25.2, TP26.2, U3.8 (VSS), U3.15 (TD), U3.17 (VSS), U8.3 (PGND), U8.9 (GND), U8.11 (PGND), U9.4 (GND), U12.2 (GND); also elsewhere on the board
unnamed: CON1.1 (POS), U3.2 (BAT), U3.3 (BAT)
unnamed: D1.1 (K), J1.A5 (CC1), R1.1
unnamed: D2.1 (K), J1.B5 (CC2), R2.1
unnamed: D37.2 (A), R8.2
unnamed: D38.2 (A), R9.2
unnamed: J5.1, SW1.1 (A), TP26.1
unnamed: R7.1, U3.12 (ILIM)
unnamed: R3.1, U3.16 (ISET)
unnamed: R4.1, U3.14 (TMR)
unnamed: R5.1, R6.2, U3.1 (TS)
unnamed: C17.1, R10.2, U8.6 (EN), U8.7 (PS/SYNC), U8.8 (VINA)
unnamed: L1.1, U8.4 (L1)
unnamed: L1.2, U8.2 (L2)
unnamed: R11.2, R12.2, U9.1 (FB)
unnamed: L2.1, U9.5 (SW)
VBUS: C1.1, C2.1, C9.1, C10.1, J1.A4 (VBUS), J1.A9 (VBUS), J1.B4 (VBUS), J1.B9 (VBUS), J4.1, R6.1, R8.1, R9.1, TP25.1, U3.13 (IN); also elsewhere on the board

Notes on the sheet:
5V Power Supply
ESD Protection Diodes (ESD321)
Power Injection Points
USB Connector
3.3V Power Supply
Battery Holder
1.8V Power Supply
Battery Charger / Power Path
Power Injection/Test Points

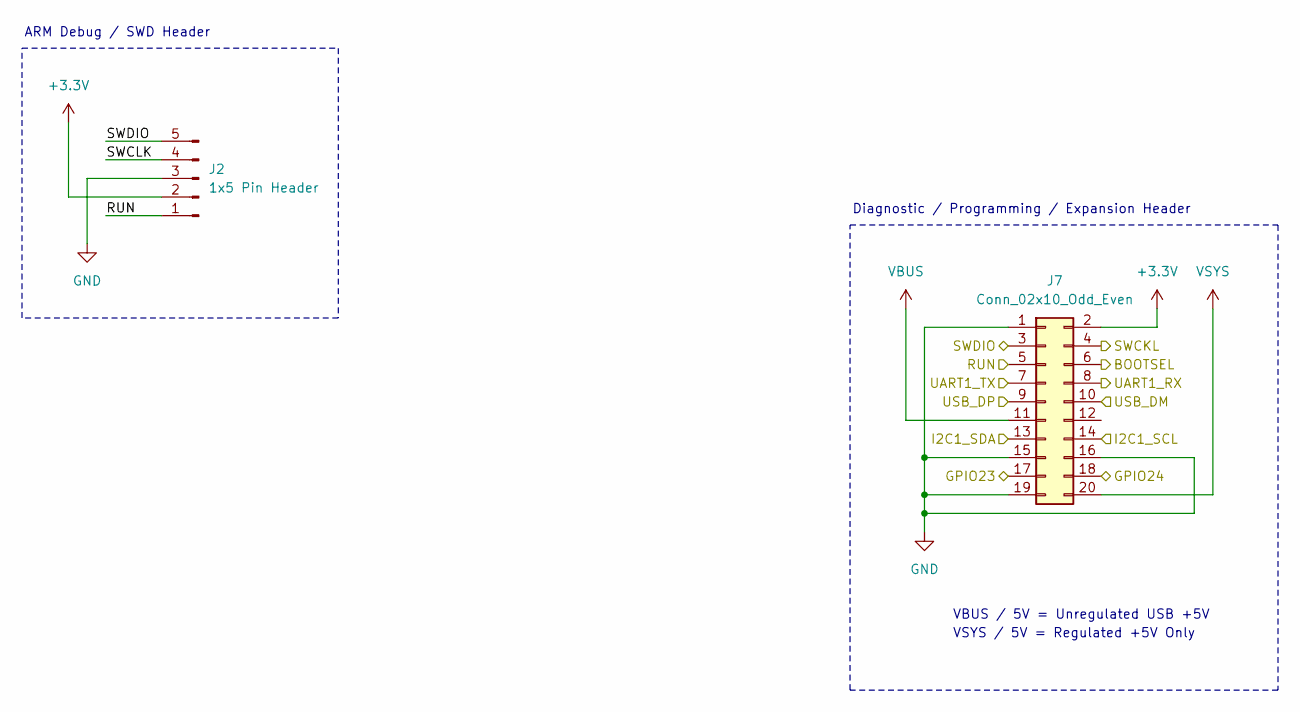
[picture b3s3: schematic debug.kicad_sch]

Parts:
J2: 1x5 Pin Header; PinHeader_1x05_P2.54mm_Vertical_SMD_Pin1Left
J7: Conn_02x10_Odd_Even; PinHeader_2x10_P2.54mm_Vertical_SMD

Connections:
+3.3V: J2.2, J7.2; also elsewhere on the board
/LED/I2C1_SCL: J7.14; also elsewhere on the board
/LED/I2C1_SDA: J7.13; also elsewhere on the board
/MCU/BOOTSEL: J7.6; also elsewhere on the board
/MCU/GPIO23: J7.17; also elsewhere on the board
/MCU/GPIO24: J7.18; also elsewhere on the board
/MCU/SWCLK: J7.4; also elsewhere on the board
/MCU/UART1_RX: J7.8; also elsewhere on the board
/MCU/UART1_TX: J7.7; also elsewhere on the board
/MCU/USB_DM: J7.10; also elsewhere on the board
/MCU/USB_DP: J7.9; also elsewhere on the board
/debug/RUN: J2.1, J7.5; also elsewhere on the board
/debug/SWCLK: J2.4
/debug/SWDIO: J2.5, J7.3; also elsewhere on the board
GND: J2.3, J7.1, J7.15, J7.16, J7.19; also elsewhere on the board
VBUS: J7.11; also elsewhere on the board

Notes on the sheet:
VBUS / 5V = Unregulated USB +5V
Diagnostic / Programming / Expansion Header
VSYS / 5V = Regulated +5V Only
ARM Debug / SWD Header
